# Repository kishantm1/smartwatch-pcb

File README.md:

# Wearable Smartwatch PCB 

Wearable smartwatch PCB based on ESP32-S3 integrating IMU-based step tracking, temperature sensing, barometric pressure sensing, Bluetooth connectivity, and display/touch interfaces. This project focused on end-to-end wearable hardware development, including BOM creation, schematic design, PCB layout, reflow soldering, board testing, and firmware development.

## Key Features

- Wrist-worn smartwatch form factor
- Touch/display interface for on-device navigation
- Main screen with time, battery status, and Bluetooth status
- Health screen with skin temperature and step tracking
- Environment screen with barometric pressure and weather
- 3.7V battery-powered design

## Hardware Architecture

The board is centered around the ESP32-S3 microcontroller and integrates sensing, display, power, and programming/debug circuitry into a compact smartwatch PCB.

- **MCU:** ESP32-S3
- **Motion sensing:** IMU for motion and step tracking
- **Environmental sensing:** Temperature sensor and barometric pressure sensor
- **Sensor communication:** I2C sensor interfaces
- **Wireless communication:** Bluetooth/BLE through the ESP32-S3
- **Display/UI:** Touchscreen display for time, health data, and environmental data
- **Display communication:** SPI display interface
- **Power:** 3.7V LiPo battery with USB-C charging and regulated 3.3V system power
- **Debug/programming:** Boot and reset support circuitry
- **Indicators:** Status LED for board/charging indication

## Schematic

### MCU

### Sensors

### Power

### Display

## Layout

The 2-layer PCB layout was designed to fit within a compact smartwatch form factor while routing sensor, display/touch, and power connections.

## 3D View

## Assembly 

The board was assembled using solder paste, manual component placement, and reflow soldering.

**Solder paste applied**

**Components placed**

**After heating in oven**

## Testing 

Initial testing focused on basic board functionality and power validation.

Testing included:
- Checking for shorts
- Verifying power delivery
- Checking sensor behavior
- Testing I2C connection to connected ICs

## Final Board

**Front side**

**Back side**

## Firmware

The firmware runs on the ESP32-S3 and ties together everything the watch does from reading sensors, driving the display, handling touch input, and communicating wirelessly over both Bluetooth and WiFi. Rather than pausing to wait on one task before starting the next, each subsystem (sensor sampling, display redraws, BLE updates) runs on its own independent timer. Sensors are read once a second, the screen redraws once a second, and BLE pushes updates every five seconds, but none of these ever block each other. Touch input is checked continuously in between, so the watch always feels responsive instead of freezing while it waits on a sensor or a network request.

### Motion Sensing & Step Tracking

Motion is measured with a 6-axis IMU (accelerometer + gyroscope), connected to the ESP32-S3 over I2C. Rather than calculating steps in software from raw motion data, the firmware offloads step detection to the pedometer algorithm built directly into the IMU itself. The IMU's embedded pedometer engine detects step patterns on-chip and maintains an internal step counter that the ESP32-S3 reads during operation. This reduces processing overhead on the ESP32-S3 by allowing the IMU's dedicated hardware engine to handle step detection.

### Temperature & Environmental Sensing

Skin temperature and barometric pressure are read from two more I2C sensors. The pressure sensor's raw reading is converted into an estimated altitude using a standard atmospheric pressure formula, since pressure decreases predictably with elevation. Both values feed directly into the on-screen health and environment displays.

### Time & Location Awareness

The watch figures out where it is and what time it is without ever needing to pair with a phone. On boot, the watch connects to WiFi and queries a geolocation API using its public IP address. This returns both approximate coordinates and a UTC time zone offset, without requiring GPS hardware. Separately, the watch syncs its clock over the network using NTP (Network Time Protocol), which provides an accurate current time from public time servers, but only in UTC. Since NTP alone doesn't know what time zone the watch is actually in, the geolocation offset is applied on top of that synced time to shift it to the correct local time. The same location lookup also feeds current local weather conditions, so a single lookup on boot supports both features and avoids relying on any hardcoded location.

### Bluetooth Connectivity

The ESP32-S3 runs a Bluetooth Low Energy (BLE) GATT server that organizes the watch's sensor data, including step count, skin temperature, pressure, and altitude, as a set of services and characteristics that any nearby device can connect to. This was confirmed using a generic BLE inspection app, LightBlue, which connected to the watch and read back the correct decoded value for each characteristic. The image shows the app discovered the watch's custom Health Service along with its four characteristics.

### Touchscreen Navigation

Navigation is handled by a capacitive touch controller, also connected over I2C. Rather than continuously polling the controller to check for input, the firmware relies on an interrupt. The touch controller itself signals the ESP32 the instant a gesture occurs. Swipe gestures move between the watch's three screens.

### On-Device Display

The firmware maintains a central watch state containing the latest sensor measurements, connectivity status, and interface state. Each screen reads from this shared state and renders the corresponding information to the display.

**Home screen: Time, Date, Bluetooth & Battery Status**

**Health screen: Step Count & Skin Temperature**

**Environment screen: Weather, Barometric Pressure & Altitude**

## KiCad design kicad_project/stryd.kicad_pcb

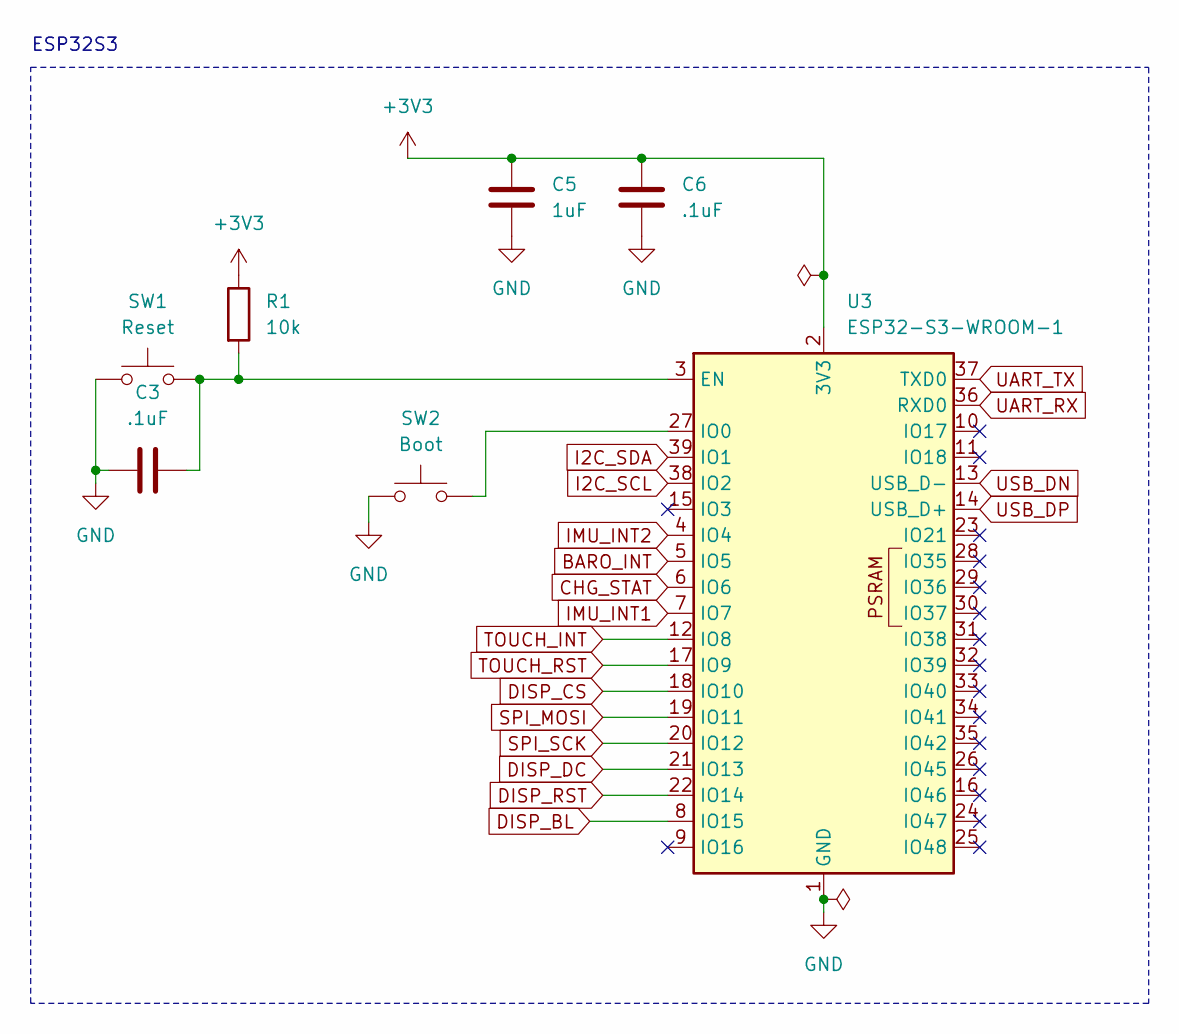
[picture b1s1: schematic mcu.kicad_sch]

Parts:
C3: .1uF; C_0805_2012Metric_Pad1.18x1.45mm_HandSolder
C5: 1uF; C_0603_1608Metric_Pad1.08x0.95mm_HandSolder
C6: .1uF; C_0603_1608Metric_Pad1.08x0.95mm_HandSolder
R1: 10k; R_0603_1608Metric_Pad0.98x0.95mm_HandSolder
SW1: Reset; SW_Push_1P1T-SH_NO_CK_KMR2xxG
SW2: Boot; SW_Push_1P1T-SH_NO_CK_KMR2xxG
U3: ESP32-S3-WROOM-1

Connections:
+3V3: C5.1, C6.1, R1.1, U3.2 (3V3); also elsewhere on the board
BARO_INT: U3.5 (IO5); also elsewhere on the board
CHG_STAT: U3.6 (IO6); also elsewhere on the board
DISP_BL: U3.8 (IO15); also elsewhere on the board
DISP_CS: U3.18 (IO10); also elsewhere on the board
DISP_DC: U3.21 (IO13); also elsewhere on the board
DISP_RST: U3.22 (IO14); also elsewhere on the board
GND: C3.1, C5.2, C6.2, SW1.1, SW2.2, U3.1 (GND), U3.40 (GND), U3.41 (GND); also elsewhere on the board
I2C_SCL: U3.38 (IO2); also elsewhere on the board
I2C_SDA: U3.39 (IO1); also elsewhere on the board
IMU_INT1: U3.7 (IO7); also elsewhere on the board
IMU_INT2: U3.4 (IO4); also elsewhere on the board
unnamed: C3.2, R1.2, SW1.2, U3.3 (EN)
unnamed: SW2.1, U3.27 (IO0)
SPI_MOSI: U3.19 (IO11); also elsewhere on the board
SPI_SCK: U3.20 (IO12); also elsewhere on the board
TOUCH_INT: U3.12 (IO8); also elsewhere on the board
TOUCH_RST: U3.17 (IO9); also elsewhere on the board
UART_RX: U3.36 (RXD0)
UART_TX: U3.37 (TXD0)
USB_DN: U3.13 (USB_D-); also elsewhere on the board
USB_DP: U3.14 (USB_D+); also elsewhere on the board

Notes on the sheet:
ESP32S3

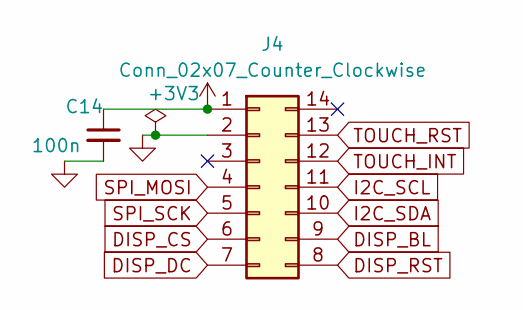
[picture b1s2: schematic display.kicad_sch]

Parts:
C14: 100n; C_0805_2012Metric_Pad1.18x1.45mm_HandSolder
J4: Conn_02x07_Counter_Clockwise; PinHeader_2x07_P2.54mm_Vertical

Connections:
+3V3: C14.1, J4.1; also elsewhere on the board
DISP_BL: J4.9; also elsewhere on the board
DISP_CS: J4.6; also elsewhere on the board
DISP_DC: J4.7; also elsewhere on the board
DISP_RST: J4.8; also elsewhere on the board
GND: C14.2, J4.2; also elsewhere on the board
I2C_SCL: J4.11; also elsewhere on the board
I2C_SDA: J4.10; also elsewhere on the board
SPI_MOSI: J4.4; also elsewhere on the board
SPI_SCK: J4.5; also elsewhere on the board
TOUCH_INT: J4.12; also elsewhere on the board
TOUCH_RST: J4.13; also elsewhere on the board

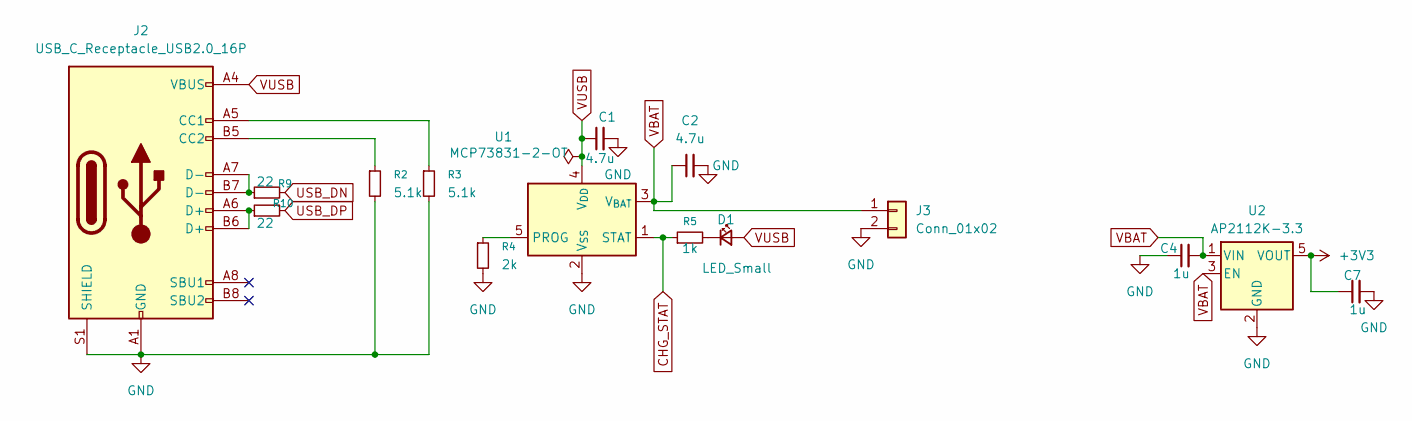
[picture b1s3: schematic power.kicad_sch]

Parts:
C1, C2: 4.7u; C_0805_2012Metric_Pad1.18x1.45mm_HandSolder
C4, C7: 1u; C_0603_1608Metric_Pad1.08x0.95mm_HandSolder
D1: LED_Small; LED_1206_3216Metric_Pad1.42x1.75mm_HandSolder
J2: USB_C_Receptacle_USB2.0_16P; USB_C_Receptacle_GCT_USB4085
J3: Conn_01x02; JST_PH_S2B-PH-K_1x02_P2.00mm_Horizontal
R2, R3: 5.1k; R_0603_1608Metric_Pad0.98x0.95mm_HandSolder
R4: 2k; R_0603_1608Metric_Pad0.98x0.95mm_HandSolder
R5: 1k; R_0603_1608Metric_Pad0.98x0.95mm_HandSolder
R9, R10: 22; R_0603_1608Metric_Pad0.98x0.95mm_HandSolder
U1: MCP73831-2-OT; SOT-23-5
U2: AP2112K-3.3; SOT-23-5

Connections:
+3V3: C7.1, U2.5 (VOUT); also elsewhere on the board
CHG_STAT: R5.1, U1.1 (STAT); also elsewhere on the board
GND: C1.2, C2.2, C4.1, C7.2, J2.A1 (GND), J2.A12 (GND), J2.B1 (GND), J2.B12 (GND), J2.S1 (SHIELD), J3.2, R2.2, R3.2, R4.2, U1.2 (V_{SS}), U2.2 (GND); also elsewhere on the board
unnamed: D1.1 (K), R5.2
unnamed: J2.A5 (CC1), R3.1
unnamed: J2.B5 (CC2), R2.1
unnamed: J2.A6 (D+), J2.B6 (D+), R10.1
unnamed: J2.A7 (D-), J2.B7 (D-), R9.1
unnamed: R4.1, U1.5 (PROG)
USB_DN: R9.2; also elsewhere on the board
USB_DP: R10.2; also elsewhere on the board
VBAT: C2.1, C4.2, J3.1, U1.3 (V_{BAT}), U2.1 (VIN), U2.3 (EN)
VUSB: C1.1, D1.2 (A), J2.A4 (VBUS), J2.A9 (VBUS), J2.B4 (VBUS), J2.B9 (VBUS), U1.4 (V_{DD})

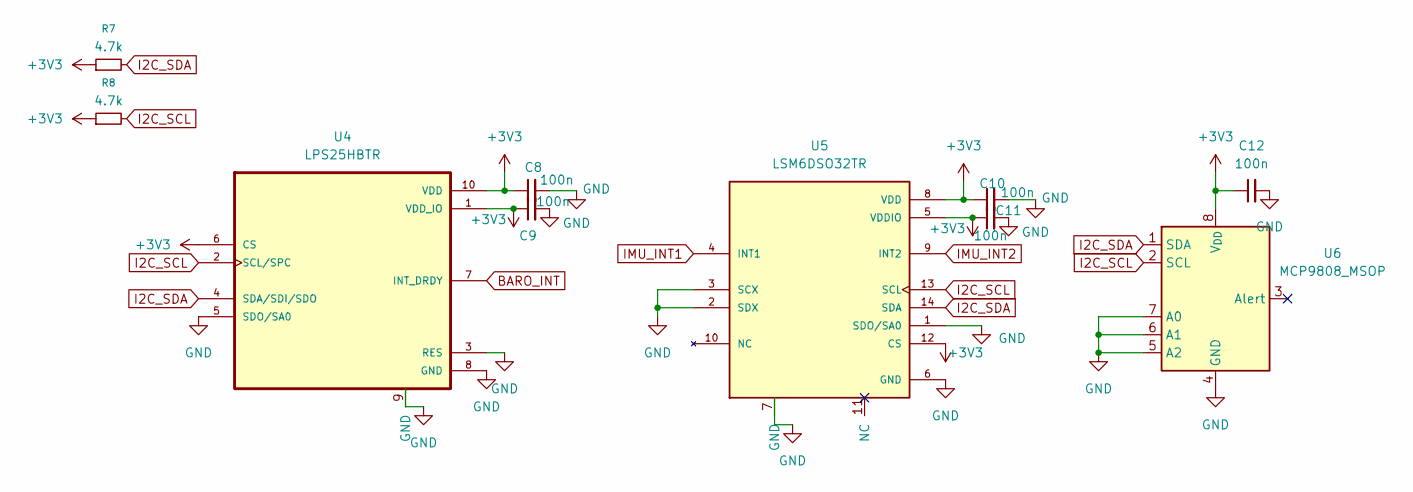
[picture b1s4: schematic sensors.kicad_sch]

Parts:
C8, C9, C10, C11, C12: 100n; C_0805_2012Metric_Pad1.18x1.45mm_HandSolder
R7, R8: 4.7k; R_0603_1608Metric_Pad0.98x0.95mm_HandSolder
U4: LPS25HBTR; HLGA10_2P5X2P5_STM_U4; PARTREV 4
U5: LSM6DSO32TR; LGA-14L_2P5X3X0P83_STM; PARTREV 1
U6: MCP9808_MSOP; MSOP-8_3x3mm_P0.65mm

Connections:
+3V3: C8.1, C9.1, C10.1, C11.1, C12.1, R7.1, R8.1, U4.1 (VDD_IO), U4.6 (CS), U4.10 (VDD), U5.5 (VDDIO), U5.8 (VDD), U5.12 (CS), U6.8 (V_{DD}); also elsewhere on the board
BARO_INT: U4.7 (INT_DRDY); also elsewhere on the board
GND: C8.2, C9.2, C10.2, C11.2, C12.2, U4.3 (RES), U4.5 (SDO/SA0), U4.8 (GND), U4.9 (GND), U5.1 (SDO/SA0), U5.2 (SDX), U5.3 (SCX), U5.6 (GND), U5.7 (GND), U6.4 (GND), U6.5 (A2), U6.6 (A1), U6.7 (A0); also elsewhere on the board
I2C_SCL: R8.2, U4.2 (SCL/SPC), U5.13 (SCL), U6.2 (SCL); also elsewhere on the board
I2C_SDA: R7.2, U4.4 (SDA/SDI/SDO), U5.14 (SDA), U6.1 (SDA); also elsewhere on the board
IMU_INT1: U5.4 (INT1); also elsewhere on the board
IMU_INT2: U5.9 (INT2); also elsewhere on the board

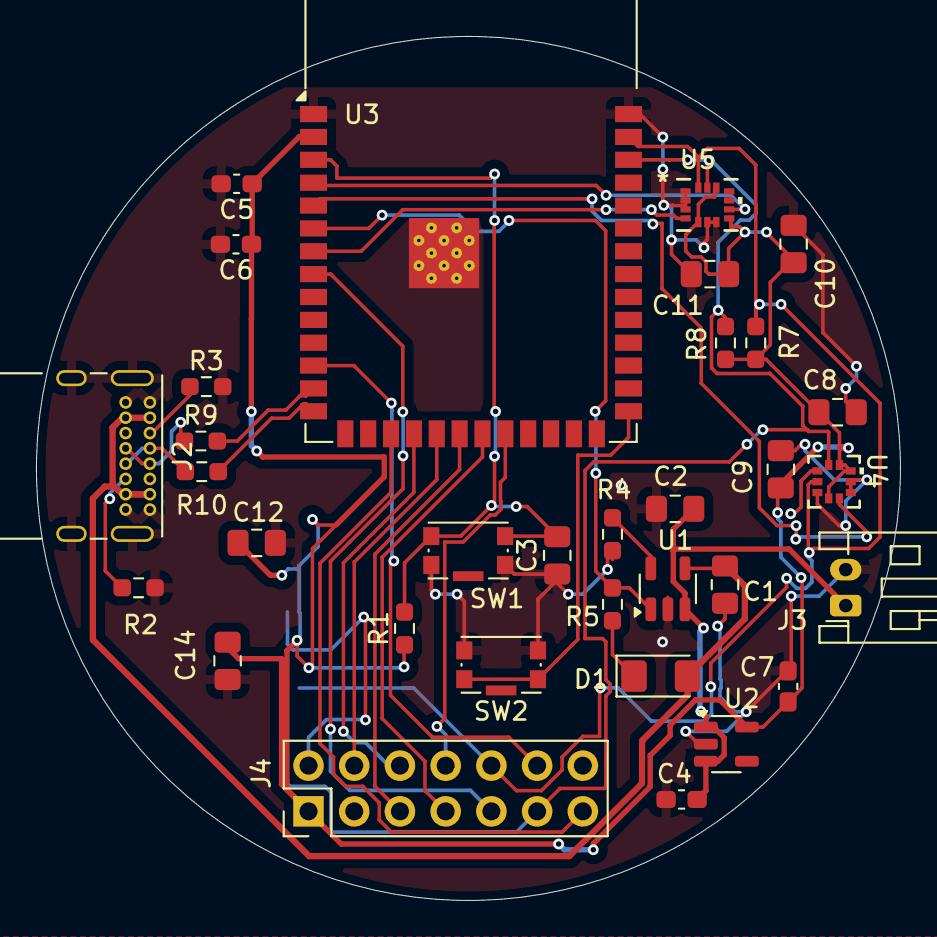
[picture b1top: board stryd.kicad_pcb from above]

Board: 2 copper layers, 48.0 x 48.0 mm, 34 parts (1 on the bottom side), 28 nets.

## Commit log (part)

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2026-06-23 Create images folder
2026-06-23 Added images
2026-06-23 Deleted image
2026-06-23 Smartwatch Images
2026-06-24 Create kicad_project
2026-06-24 KiCad Files
2026-06-24 Library.pretty
2026-06-24 Create libraries
2026-06-24 Libraries
2026-06-24 Add image
